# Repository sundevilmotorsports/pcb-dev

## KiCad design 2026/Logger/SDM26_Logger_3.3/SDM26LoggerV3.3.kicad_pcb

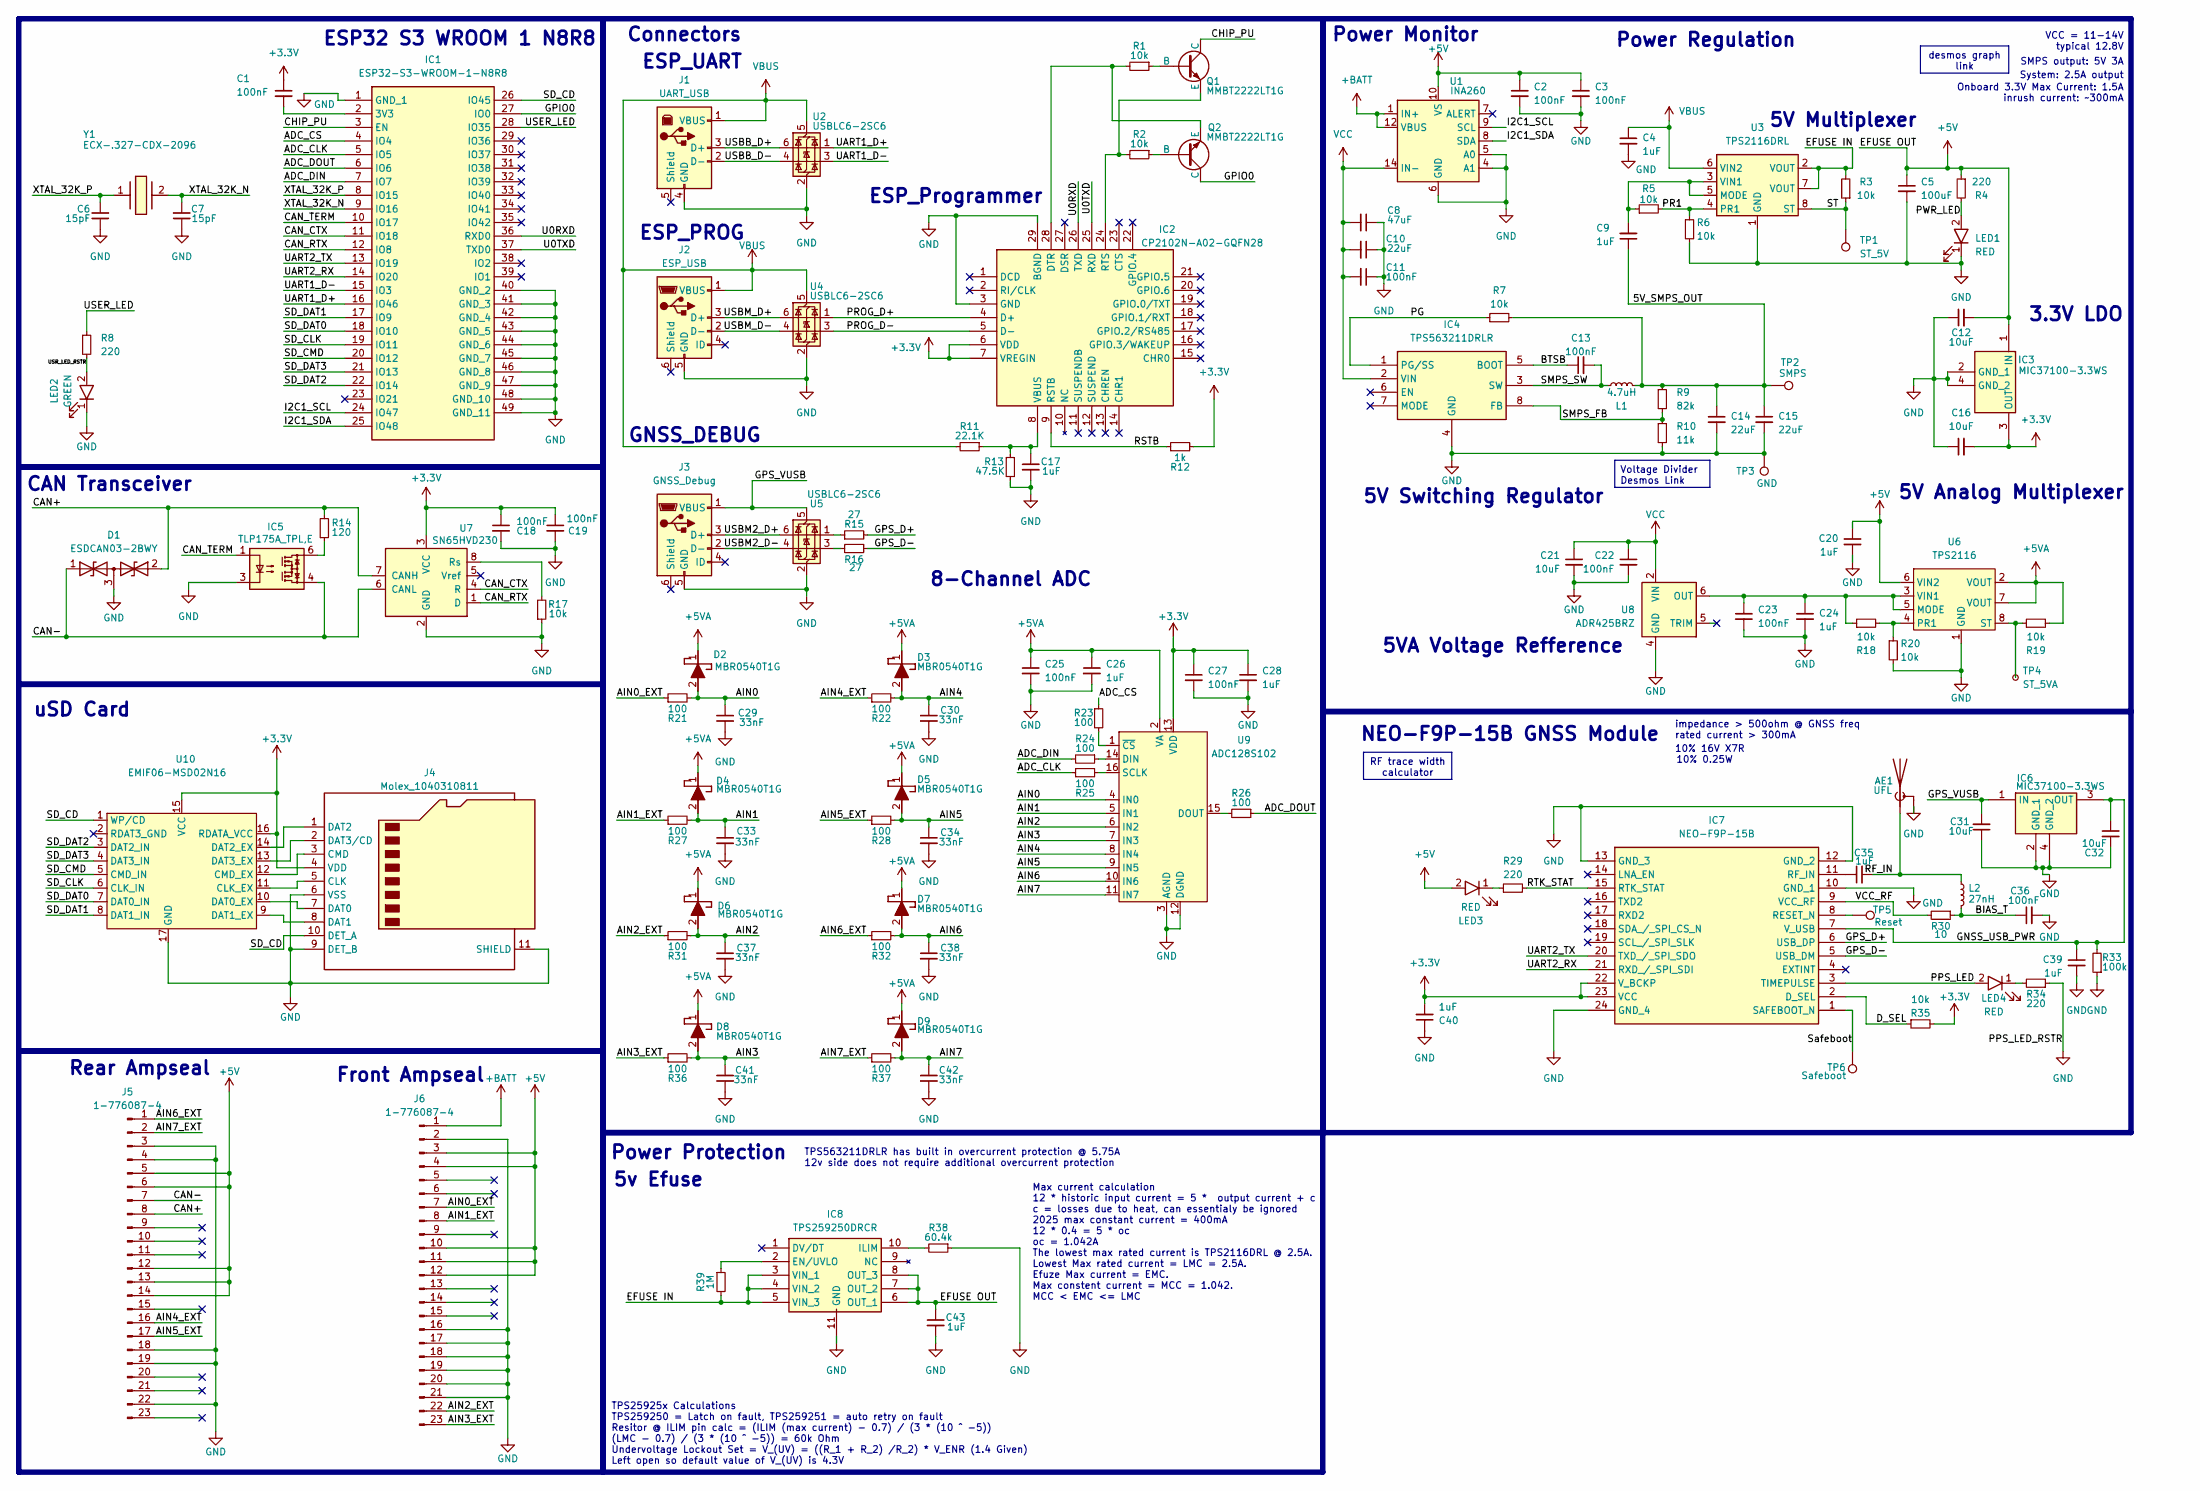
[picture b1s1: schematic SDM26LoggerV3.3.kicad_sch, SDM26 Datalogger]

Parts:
AE1: UFL; U.FL_Molex_MCRF_73412-0110_Vertical
C1, C2, C3, C11, C13, C18, C19, C22, C23, C25, C27, C36: 100nF; C_0603_1608Metric
C4, C9, C17, C20, C24, C26, C28, C35, C39, C40, C43: 1uF; C_0603_1608Metric
C5: 100uF; CP_Elec_6.3x5.9
C6, C7: 15pF; C_0603_1608Metric
C8: 47uF; CP_Elec_6.3x5.9
C10, C14, C15: 22uF; C_0603_1608Metric
C12, C16, C21, C31, C32: 10uF; C_0603_1608Metric
C29, C30, C33, C34, C37, C38, C41, C42: 33nF; C_0603_1608Metric
D1: ESDCAN03-2BWY; SOT65P210X110-3N; Mouser Part Number 511-ESDCAN03-2BWY
D2, D3, D4, D5, D6, D7, D8, D9: MBR0540T1G; SOD3716X135N; Mouser Part Number 863-MBR0540T1G
IC1: ESP32-S3-WROOM-1-N8R8; ESP32S3WROOM1N8R8; Mouser Part Number 356-EP32S3WROOM1N8R8
IC2: CP2102N-A02-GQFN28; QFN50P500X500X80-29N-D; Mouser Part Number 634-CP2102NA02GQFN28
IC3, IC6: MIC37100-3.3WS; SOT230P700X180-4N; Mouser Part Number 998-MIC37100-3.3WS
IC4: TPS563211DRLR; SOTFL50P160X60-8N; Mouser Part Number 595-TPS563211DRLR
IC5: TLP175A_TPL,E; TLP266J; Mouser Part Number 757-TLP175A(TPLE
IC7: NEO-F9P-15B; NEOF9P15B; Mouser Part Number 377-NEO-F9P-15B
IC8: TPS259250DRCR; SON50P300X300X100-11L-D; Mouser Part Number 595-TPS259250DRCR
J1: UART_USB; 67068-7041
J2: ESP_USB; USB_Micro-B_Molex-105017-0001
J3: GNSS_Debug; USB_Micro-B_Molex-105017-0001
J4: Molex_1040310811; microSD_HC_Molex_104031-0811
J5, J6: 1-776087-4; CONN23_776087_TEC
L1: 4.7uH; L_Bourns_SRP7028A_7.3x6.6mm
L2: 27nH; L_0402_1005Metric
LED1, LED3, LED4: RED; SSFLXH100LID01; Mouser Part Number 696-SSFLXH100LID01
LED2: GREEN; SSFLXH100LID01; Mouser Part Number 696-SSFLXH100LID01
Q1, Q2: MMBT2222LT1G; SOT96P237X111-3N
R1, R2, R3, R5, R6, R7, R17, R18, R19, R20, R35: 10k; R_0603_1608Metric
R4, R8, R29, R34: 220; R_0603_1608Metric
R9: 82k; R_0603_1608Metric
R10: 11k; R_0603_1608Metric
R11: 22.1K; R_0603_1608Metric
R12: 1k; R_0603_1608Metric
R13: 47.5K; R_0603_1608Metric
R14: 120; R_0603_1608Metric
R15, R16: 27; R_0603_1608Metric
R21, R22, R23, R24, R25, R26, R27, R28, R31, R32, R36, R37: 100; R_0603_1608Metric
R30: 10; R_0603_1608Metric
R33: 100k; R_0603_1608Metric
R38: 60.4k; R_0603_1608Metric
R39: 1M; R_0603_1608Metric
TP1: ST_5V; TestPoint_Pad_1.5x1.5mm
TP2: SMPS; TestPoint_Pad_1.5x1.5mm
TP3: GND; TestPoint_Pad_1.5x1.5mm
TP4: ST_5VA; TestPoint_Pad_1.5x1.5mm
TP5: Reset; TestPoint_Pad_1.5x1.5mm
TP6: Safeboot; TestPoint_Pad_1.5x1.5mm
U1: INA260; TSSOP-16_4.4x5mm_P0.65mm
U2, U4, U5: USBLC6-2SC6; SOT-23-6
U3: TPS2116DRL; SOT-583-8
U6: TPS2116; SOT-5X3
U7: SN65HVD230; SOIC-8_3.9x4.9mm_P1.27mm
U8: ADR425BRZ; SOIC-8_3.9x4.9mm_P1.27mm
U9: ADC128S102; TSSOP-16_4.4x5mm_P0.65mm
U10: EMIF06-MSD02N16; UQFN-17-3.5x1.2mm
Y1: ECX-.327-CDX-2096; ECX327CDX2096; Mouser Part Number 520-X-.327-CDX2096

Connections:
+3.3V: C1.1, C16.2, C18.1, C19.1, C27.1, C28.1, C40.2, IC2.6 (VDD), IC2.7 (VREGIN), IC3.3 (OUT), IC7.22 (V_BCKP), IC7.23 (VCC), J4.4 (VDD), R12.2, R35.2, U7.3 (VCC), U9.13 (VDD), U10.15 (VCC), U10.16 (RDATA_VCC)
+5V: C2.1, C3.1, C5.1, C12.2, C20.1, C43.1, IC3.1 (IN), IC8.6 (OUT_1), IC8.7 (OUT_2), IC8.8 (OUT_3), J5.5, J5.6, J5.12, J5.13, J5.14, J6.3, J6.4, J6.10, J6.11, J6.12, LED3.2 (A), R4.1, U1.10 (VS), U6.6 (VIN2)
+5VA: C25.1, C26.1, D2.1 (K), D3.1 (K), D4.1 (K), D5.1 (K), D6.1 (K), D7.1 (K), D8.1 (K), D9.1 (K), R19.2, U6.2 (VOUT), U6.7 (VOUT), U9.2 (VA)
+BATT: J6.1, U1.1 (IN+), U1.2 (IN+), U1.3 (IN+), U1.12 (VBUS)
/5V_SMPS_OUT: C9.1, C14.1, C15.1, L1.1, R7.2, R9.1, TP2.1
/ADC_CLK: IC1.5 (IO5), R25.1
/ADC_CS: IC1.4 (IO4), R23.1
/ADC_DIN: IC1.7 (IO7), R24.2
/ADC_DOUT: IC1.6 (IO6), R26.1
/AIN0: C29.1, D2.2 (A), R21.2, U9.4 (IN0)
/AIN0_EXT: J6.7, R21.1
/AIN1: C33.1, D4.2 (A), R27.2, U9.5 (IN1)
/AIN1_EXT: J6.8, R27.1
/AIN2: C37.1, D6.2 (A), R31.2, U9.6 (IN2)
/AIN2_EXT: J6.22, R31.1
/AIN3: C41.1, D8.2 (A), R36.2, U9.7 (IN3)
/AIN3_EXT: J6.23, R36.1
/AIN4: C30.1, D3.2 (A), R22.2, U9.8 (IN4)
/AIN4_EXT: J5.16, R22.1
/AIN5: C34.1, D5.2 (A), R28.2, U9.9 (IN5)
/AIN5_EXT: J5.17, R28.1
/AIN6: C38.1, D7.2 (A), R32.2, U9.10 (IN6)
/AIN6_EXT: J5.1, R32.1
/AIN7: C42.1, D9.2 (A), R37.2, U9.11 (IN7)
/AIN7_EXT: J5.2, R37.1
/BIAS_T: C36.1, L2.2, R30.1
/BTSB: C13.1, IC4.5 (BOOT)
/CAN+: D1.2, J5.8, R14.2, U7.7 (CANH)
/CAN-: D1.1, IC5.4, J5.7, U7.6 (CANL)
/CAN_CTX: IC1.11 (IO18), U7.4 (R)
/CAN_RTX: IC1.12 (IO8), U7.1 (D)
/CAN_TERM: IC1.10 (IO17), IC5.1
/CHIP_PU: IC1.3 (EN), Q1.1 (C)
/D_SEL: IC7.2 (D_SEL), R35.1
/EFUSE IN: IC8.3 (VIN_1), IC8.4 (VIN_2), IC8.5 (VIN_3), R3.2, R39.2, U3.2 (VOUT), U3.7 (VOUT)
/GNSS_USB_PWR: C32.1, C39.1, IC6.3 (OUT), IC7.7 (V_USB), R33.2
/GPIO0: IC1.27 (IO0), Q2.1 (C)
/GPS_D+: IC7.6 (USB_DP), R15.2
/GPS_D-: IC7.5 (USB_DM), R16.1
/GPS_VUSB: C31.2, IC6.1 (IN), J3.1 (VBUS), U5.5 (VBUS); also elsewhere on the board
/I2C1_SCL: IC1.24 (IO47), U1.9 (SCL)
/I2C1_SDA: IC1.25 (IO48), U1.8 (SDA)
/PG: IC4.1 (PG/SS), R7.1
/PPS_LED: IC7.3 (TIMEPULSE), LED4.2 (A)
/PR1: R5.2, R6.1, U3.4 (PR1)
/PROG_D+: IC2.4 (D+), U4.1 (I/O1)
/PROG_D-: IC2.5 (D-), U4.3 (I/O2)
/PWR_LED: LED1.2 (A), R4.2
/RF_IN: AE1.1 (A), C35.2, L2.1
/RSTB: IC2.9 (RSTB), R12.1
/RTK_STAT: IC7.15 (RTK_STAT), R29.2
/SD_CD: IC1.26 (IO45), J4.10 (DET_A), U10.1 (WP/CD)
/SD_CLK: IC1.19 (IO11), U10.6 (CLK_IN)
/SD_CMD: IC1.20 (IO12), U10.5 (CMD_IN)
/SD_DAT0: IC1.18 (IO10), U10.7 (DAT0_IN)
/SD_DAT1: IC1.17 (IO9), U10.8 (DAT1_IN)
/SD_DAT2: IC1.22 (IO14), U10.3 (DAT2_IN)
/SD_DAT3: IC1.21 (IO13), U10.4 (DAT3_IN)
/SMPS_FB: IC4.8 (FB), R9.2, R10.1
/SMPS_SW: C13.2, IC4.3 (SW), L1.2
/ST: R3.1, TP1.1, U3.8 (ST)
/Safeboot: IC7.1 (SAFEBOOT_N), TP6.1
/U0RXD: IC1.36 (RXD0), IC2.26 (TXD)
/U0TXD: IC1.37 (TXD0), IC2.25 (RXD)
/UART1_D+: IC1.16 (IO46), U2.1 (I/O1)
/UART1_D-: IC1.15 (IO3), U2.3 (I/O2)
/UART2_RX: IC1.14 (IO20), IC7.21 (RXD_/_SPI_SDI)
/UART2_TX: IC1.13 (IO19), IC7.20 (TXD_/_SPI_SDO)
/USBB_D+: J1.3 (D+), U2.6 (I/O1)
/USBB_D-: J1.2 (D-), U2.4 (I/O2)
/USBM2_D+: J3.3 (D+), U5.6 (I/O1)
/USBM2_D-: J3.2 (D-), U5.4 (I/O2)
/USBM_D+: J2.3 (D+), U4.6 (I/O1)
/USBM_D-: J2.2 (D-), U4.4 (I/O2)
/USER_LED: IC1.28 (IO35), R8.1
/USR_LED_RSTR: LED2.2 (A), R8.2
/VCC_RF: IC7.9 (VCC_RF), R30.2
/XTAL_32K_N: C7.2, IC1.9 (IO16), Y1.2
/XTAL_32K_P: C6.2, IC1.8 (IO15), Y1.1
GND: AE1.2 (Shield), C2.2, C3.2, C4.2, C5.2, C6.1, C7.1, C8.1, C10.1, C11.1, C12.1, C14.2, C15.2, C16.1, C17.2, C18.2, C19.2, C20.2, C21.2, C22.2, C23.2, C24.2, C25.2, C26.2, C27.2, C28.2, C29.2, C30.2, C31.1, C32.2, C33.2, C34.2, C36.2, C37.2, C38.2, C39.2, C40.1, C41.2, C42.2, C43.2, D1.3, IC1.1 (GND_1), IC1.40 (GND_2), IC1.41 (GND_3), IC1.42 (GND_4), IC1.43 (GND_5), IC1.44 (GND_6), IC1.45 (GND_7), IC1.46 (GND_8), IC1.47 (GND_9), IC1.48 (GND_10), IC1.49 (GND_11), IC2.3 (GND), IC2.29 (BGND), IC3.2 (GND_1), IC3.4 (GND_2), IC4.4 (GND), IC5.3, IC6.2 (GND_1), IC6.4 (GND_2), IC7.10 (GND_1), IC7.12 (GND_2), IC7.13 (GND_3), IC7.24 (GND_4), IC8.11 (GND), J1.4 (GND), J2.5 (GND), J3.5 (GND), J4.6 (VSS), J4.9 (DET_B), J4.11 (SHIELD), J5.3, J5.4, J5.18, J5.19, J5.22, J6.2, J6.16, J6.17, J6.18, J6.19, J6.20, J6.21, LED1.1 (K), LED2.1 (K), R6.2, R10.2, R13.2, R17.1, R20.2, R33.1, R34.1, R38.1, TP3.1, U1.4 (A1), U1.5 (A0), U1.6 (GND), U1.11 (GND), U2.2 (GND), U3.1 (GND), U4.2 (GND), U5.2 (GND), U6.1 (GND), U7.2 (GND), U8.4 (GND), U9.3 (AGND), U9.12 (DGND), U10.17 (GND); also elsewhere on the board
unnamed: C1.2, IC1.2 (3V3)
unnamed: IC2.28 (DTR), Q2.3 (E), R1.2
unnamed: IC2.24 (RTS), Q1.3 (E), R2.2
unnamed: C17.1, IC2.8 (VBUS), R11.1, R13.1
unnamed: IC5.6, R14.1
unnamed: IC7.8 (RESET_N), TP5.1
unnamed: C35.1, IC7.11 (RF_IN)
unnamed: IC8.2 (EN/UVLO), R39.1
unnamed: IC8.10 (ILIM), R38.2
unnamed: J4.5 (CLK), U10.11 (CLK_EX)
unnamed: J4.3 (CMD), U10.12 (CMD_EX)
unnamed: J4.7 (DAT0), U10.10 (DAT0_EX)
unnamed: J4.8 (DAT1), U10.9 (DAT1_EX)
unnamed: J4.1 (DAT2), U10.14 (DAT2_EX)
unnamed: J4.2 (DAT3/CD), U10.13 (DAT3_EX)
unnamed: LED3.1 (K), R29.1
unnamed: LED4.1 (K), R34.2
unnamed: Q1.2 (B), R1.1
unnamed: Q2.2 (B), R2.1
unnamed: R15.1, U5.1 (I/O1)
unnamed: R16.2, U5.3 (I/O2)
unnamed: C9.2, R5.1, U3.3 (VIN1), U3.5 (MODE)
unnamed: C23.1, C24.1, R18.1, U6.3 (VIN1), U6.5 (MODE), U8.6 (OUT)
unnamed: R18.2, R20.1, U6.4 (PR1)
unnamed: R19.1, TP4.1, U6.8 (ST)
unnamed: R17.2, U7.8 (Rs)
unnamed: R24.1, U9.14 (DIN)
unnamed: R26.2, U9.15 (DOUT)
unnamed: R25.2, U9.16 (SCLK)
unnamed: R23.2, U9.1 (~CS)
VBUS: C4.1, J1.1 (VBUS), J2.1 (VBUS), R11.2, U2.5 (VBUS), U3.6 (VIN2), U4.5 (VBUS); also elsewhere on the board
VCC: C8.2, C10.2, C11.2, C21.1, C22.1, IC4.2 (VIN), U1.14 (IN-), U1.15 (IN-), U1.16 (IN-), U8.2 (VIN)

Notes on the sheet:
Power Regulation
5V Multiplexer
CAN Transceiver
10% 16V X7R
5v Efuse
inrush current: ~300mA
5V Switching Regulator
5V Analog Multiplexer
ESP32 S3 WROOM 1 N8R8
Power Monitor
Connectors
10% 0.25W
ESP_PROG
Onboard 3.3V Max Current: 1.5A
impedance > 500ohm @ GNSS freq rated current > 300mA
Front Ampseal
3.3V LDO
VCC = 11-14V typical 12.8V
GNSS_DEBUG
Max current calculation 12 * historic input current = 5 * output current + c c = losses due to heat, can essentialy be ignored 2025 max constant current = 400mA 12 * 0.4 = 5 * oc oc = 1.042A The lowest max rated current is TPS2116DRL @ 2.5A. Lowest Max rated current = LMC = 2.5A. Efuze Max current 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
ESP_UART
TPS563211DRLR has built in overcurrent protection @ 5.75A 12v side does not require additional overcurrent protection
8-Channel ADC
uSD Card
ESP_Programmer
Power Protection
5VA Voltage Refference
SMPS output: 5V 3A
NEO-F9P-15B GNSS Module
System: 2.5A output
Rear Ampseal
TPS25925x Calculations TPS259250 = Latch on fault, TPS259251 = auto retry on fault Resitor @ ILIM pin calc = (ILIM (max current) - 0.7) / (3 * (10 ^ -5)) (LMC - 0.7) / (3 * (10 ^ -5)) = 60k Ohm Undervoltage Lockout Set = V_(UV) = ((R_1 + R_2) /R_2) * V_ENR (1.4 Given) Left open so default value of 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
desmos graph link
Voltage Divider Desmos Link
RF trace width calculator

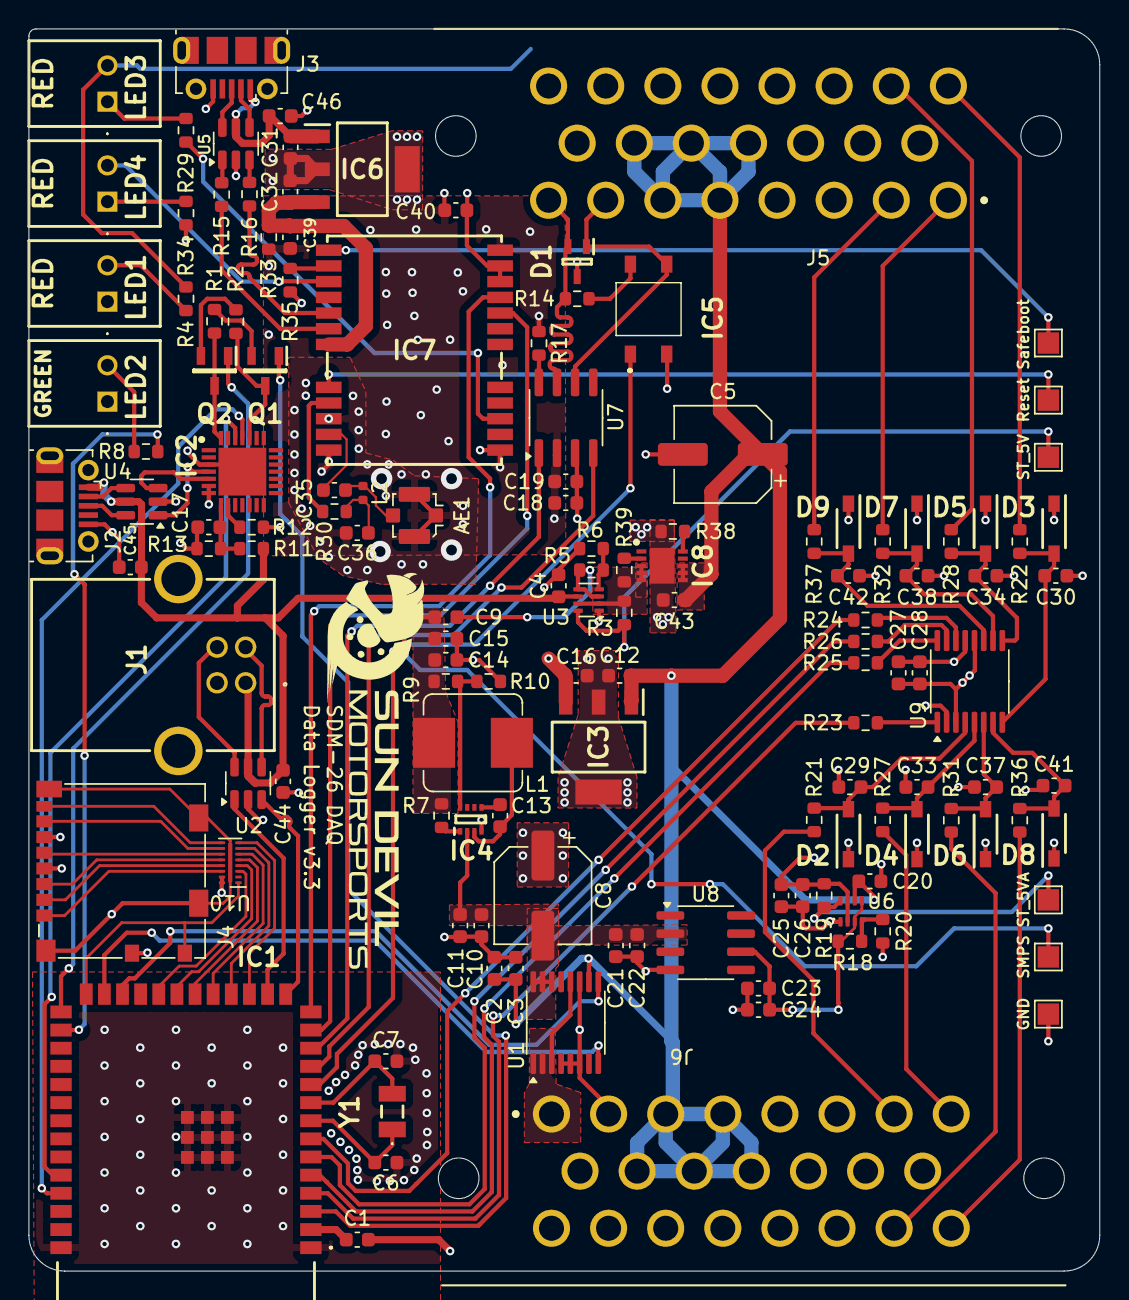
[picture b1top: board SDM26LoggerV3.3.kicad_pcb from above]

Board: 4 copper layers, 75.0 x 87.0 mm, 134 parts (0 on the bottom side), 112 nets.

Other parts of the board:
C44, C45, C46: 100nF; C_0603_1608Metric

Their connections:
/GPS_VUSB: C46.2; also elsewhere on the board
GND: C44.1, C45.1, C46.1; also elsewhere on the board
VBUS: C44.2, C45.2; also elsewhere on the board

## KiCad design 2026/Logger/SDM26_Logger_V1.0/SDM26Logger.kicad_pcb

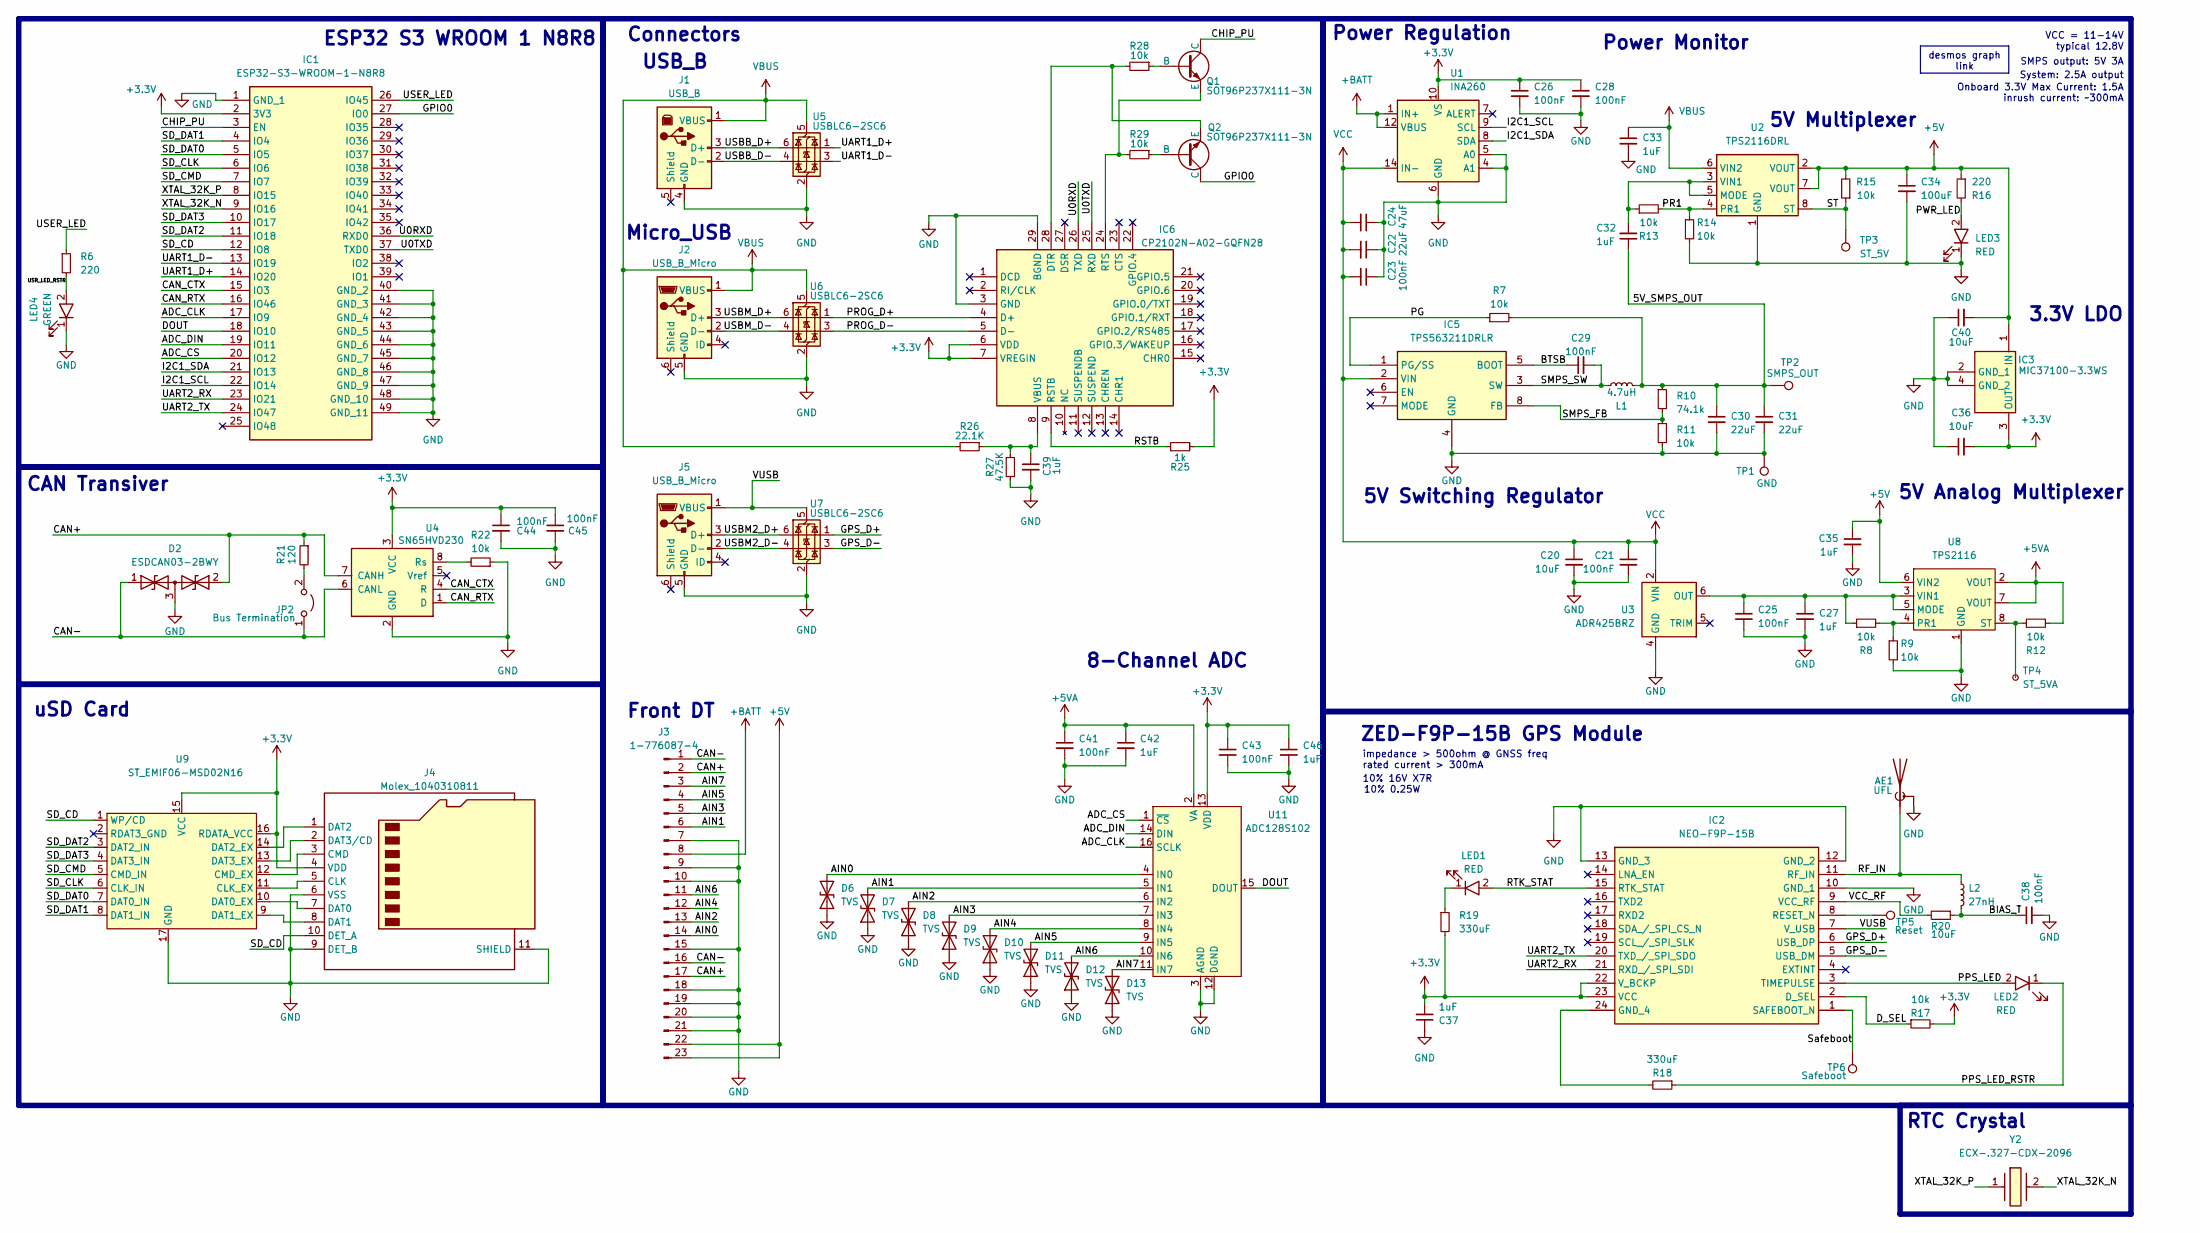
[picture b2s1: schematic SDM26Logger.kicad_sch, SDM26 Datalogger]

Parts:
AE1: UFL; U.FL_Molex_MCRF_73412-0110_Vertical
C20, C36, C40: 10uF; C_0603_1608Metric
C21, C23, C25, C26, C28, C29, C38, C41, C43, C44, C45: 100nF; C_0603_1608Metric
C22, C30, C31: 22uF; C_0603_1608Metric
C24: 47uF; CP_Elec_6.3x5.9
C27, C32, C33, C35, C37, C39, C42, C46: 1uF; C_0603_1608Metric
C34: 100uF; CP_Elec_6.3x5.9
D2: ESDCAN03-2BWY; SOT65P210X110-3N; Mouser Part Number 511-ESDCAN03-2BWY
D6, D7, D8, D9, D10, D11, D12, D13: TVS; D_SOD-323
IC1: ESP32-S3-WROOM-1-N8R8; ESP32S3WROOM1N8R8; Mouser Part Number 356-EP32S3WROOM1N8R8
IC2: NEO-F9P-15B; NEOF9P15B; Mouser Part Number 377-NEO-F9P-15B
IC3: MIC37100-3.3WS; SOT230P700X180-4N; Mouser Part Number 998-MIC37100-3.3WS
IC5: TPS563211DRLR; SOTFL50P160X60-8N; Mouser Part Number 595-TPS563211DRLR
IC6: CP2102N-A02-GQFN28; QFN50P500X500X80-29N-D; Mouser Part Number 634-CP2102NA02GQFN28
J1: USB_B; 67068-7041
J2, J5: USB_B_Micro; USB_Micro-B_Molex-105017-0001
J3: 1-776087-4; CONN23_776087_TEC
J4: Molex_1040310811; microSD_HC_Molex_104031-0811
JP2: Bus Termination; PinHeader_1x02_P2.54mm_Vertical
L1: 4.7uH; L_Bourns_SRP7028A_7.3x6.6mm
L2: 27nH; L_0402_1005Metric
LED1, LED2, LED3: RED; SSFLXH100LID01; Mouser Part Number 696-SSFLXH100LID01
LED4: GREEN; SSFLXH100LID01; Mouser Part Number 696-SSFLXH100LID01
Q1, Q2: SOT96P237X111-3N
R6, R16: 220; R_0603_1608Metric
R7, R11, R12, R13, R14, R15, R17, R22, R28, R29: 10k; R_0603_1608Metric
R8, R9: 10k; R_0402_1005Metric
R10: 74.1k; R_0603_1608Metric
R18, R19: 330uF; R_0603_1608Metric
R20: 10uF; R_0603_1608Metric
R21: 120; R_0603_1608Metric
R25: 1k; R_0603_1608Metric
R26: 22.1K; R_0603_1608Metric
R27: 47.5K; R_0603_1608Metric
TP1: GND; TestPoint_Pad_1.5x1.5mm
TP2: SMPS_OUT; TestPoint_Pad_1.5x1.5mm
TP3: ST_5V; TestPoint_Pad_1.5x1.5mm
TP4: ST_5VA; TestPoint_Pad_1.5x1.5mm
TP5: Reset; TestPoint_Pad_1.5x1.5mm
TP6: Safeboot; TestPoint_Pad_1.5x1.5mm
U1: INA260; TSSOP-16_4.4x5mm_P0.65mm
U2: TPS2116DRL; SOT-583-8
U3: ADR425BRZ; SOIC-8_3.9x4.9mm_P1.27mm
U4: SN65HVD230; SOIC-8_3.9x4.9mm_P1.27mm
U5, U6, U7: USBLC6-2SC6; SOT-23-6
U8: TPS2116; SOT-5X3
U9: ST_EMIF06-MSD02N16; UQFN-17-3.5x1.2mm
U11: ADC128S102; TSSOP-16_4.4x5mm_P0.65mm
Y2: ECX-.327-CDX-2096; ECX327CDX2096; Mouser Part Number 520-X-.327-CDX2096

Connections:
+3.3V: C26.1, C28.1, C36.2, C37.2, C43.1, C44.1, C45.1, C46.1, IC1.2 (3V3), IC2.22 (V_BCKP), IC2.23 (VCC), IC3.3 (OUT), IC6.6 (VDD), IC6.7 (VREGIN), J4.4 (VDD), R17.2, R19.2, R25.2, U1.10 (VS), U4.3 (VCC), U9.15 (VCC), U9.16 (RDATA_VCC), U11.13 (VDD)
+5V: C34.1, C35.1, C40.2, IC3.1 (IN), J3.22, J3.23, R15.2, R16.1, U2.2 (VOUT), U2.7 (VOUT), U8.6 (VIN2)
+5VA: C41.1, C42.1, R12.2, U8.2 (VOUT), U8.7 (VOUT), U11.2 (VA)
+BATT: J3.8, U1.1 (IN+), U1.2 (IN+), U1.3 (IN+), U1.12 (VBUS)
/5V_SMPS_OUT: C30.1, C31.1, C32.1, L1.1, R7.2, R10.1, TP2.1
/ADC_CLK: IC1.17 (IO9), U11.16 (SCLK)
/ADC_CS: IC1.20 (IO12), U11.1 (~CS)
/ADC_DIN: IC1.19 (IO11), U11.14 (DIN)
/AIN0: D6.2 (A2), J3.14, U11.4 (IN0)
/AIN1: D7.2 (A2), J3.6, U11.5 (IN1)
/AIN2: D8.2 (A2), J3.13, U11.6 (IN2)
/AIN3: D9.2 (A2), J3.5, U11.7 (IN3)
/AIN4: D10.2 (A2), J3.12, U11.8 (IN4)
/AIN5: D11.2 (A2), J3.4, U11.9 (IN5)
/AIN6: D12.2 (A2), J3.11, U11.10 (IN6)
/AIN7: D13.2 (A2), J3.3, U11.11 (IN7)
/BIAS_T: C38.1, L2.2, R20.1
/BTSB: C29.1, IC5.5 (BOOT)
/CAN+: D2.2, J3.2, J3.17, R21.1, U4.7 (CANH)
/CAN-: D2.1, J3.1, J3.16, JP2.1 (A), U4.6 (CANL)
/CAN_CTX: IC1.15 (IO3), U4.4 (R)
/CAN_RTX: IC1.16 (IO46), U4.1 (D)
/CHIP_PU: IC1.3 (EN), Q1.1 (C)
/DOUT: IC1.18 (IO10), U11.15 (DOUT)
/D_SEL: IC2.2 (D_SEL), R17.1
/GPIO0: IC1.27 (IO0), Q2.1 (C)
/GPS_D+: IC2.6 (USB_DP), U7.1 (I/O1)
/GPS_D-: IC2.5 (USB_DM), U7.3 (I/O2)
/I2C1_SCL: IC1.22 (IO14), U1.9 (SCL)
/I2C1_SDA: IC1.21 (IO13), U1.8 (SDA)
/PG: IC5.1 (PG/SS), R7.1
/PPS_LED: IC2.3 (TIMEPULSE), LED2.2 (A)
/PPS_LED_RSTR: LED2.1 (K), R18.1
/PR1: R13.2, R14.1, U2.4 (PR1)
/PROG_D+: IC6.4 (D+), U6.1 (I/O1)
/PROG_D-: IC6.5 (D-), U6.3 (I/O2)
/PWR_LED: LED3.2 (A), R16.2
/RF_IN: AE1.1 (A), IC2.11 (RF_IN), L2.1
/RSTB: IC6.9 (RSTB), R25.1
/RTK_STAT: IC2.15 (RTK_STAT), LED1.2 (A)
/SD_CD: IC1.12 (IO8), J4.10 (DET_A), U9.1 (WP/CD)
/SD_CLK: IC1.6 (IO6), U9.6 (CLK_IN)
/SD_CMD: IC1.7 (IO7), U9.5 (CMD_IN)
/SD_DAT0: IC1.5 (IO5), U9.7 (DAT0_IN)
/SD_DAT1: IC1.4 (IO4), U9.8 (DAT1_IN)
/SD_DAT2: IC1.11 (IO18), U9.3 (DAT2_IN)
/SD_DAT3: IC1.10 (IO17), U9.4 (DAT3_IN)
/SMPS_FB: IC5.8 (FB), R10.2, R11.1
/SMPS_SW: C29.2, IC5.3 (SW), L1.2
/ST: R15.1, TP3.1, U2.8 (ST)
/Safeboot: IC2.1 (SAFEBOOT_N), TP6.1
/U0RXD: IC1.36 (RXD0), IC6.26 (TXD)
/U0TXD: IC1.37 (TXD0), IC6.25 (RXD)
/UART1_D+: IC1.14 (IO20), U5.1 (I/O1)
/UART1_D-: IC1.13 (IO19), U5.3 (I/O2)
/UART2_RX: IC1.23 (IO21), IC2.21 (RXD_/_SPI_SDI)
/UART2_TX: IC1.24 (IO47), IC2.20 (TXD_/_SPI_SDO)
/USBB_D+: J1.3 (D+), U5.6 (I/O1)
/USBB_D-: J1.2 (D-), U5.4 (I/O2)
/USBM2_D+: J5.3 (D+), U7.6 (I/O1)
/USBM2_D-: J5.2 (D-), U7.4 (I/O2)
/USBM_D+: J2.3 (D+), U6.6 (I/O1)
/USBM_D-: J2.2 (D-), U6.4 (I/O2)
/USER_LED: IC1.26 (IO45), R6.1
/USR_LED_RSTR: LED4.2 (A), R6.2
/VCC_RF: IC2.9 (VCC_RF), R20.2
/VUSB: IC2.7 (V_USB), J5.1 (VBUS), U7.5 (VBUS)
/XTAL_32K_N: IC1.9 (IO16), Y2.2
/XTAL_32K_P: IC1.8 (IO15), Y2.1
GND: AE1.2 (Shield), C20.2, C21.2, C22.1, C23.1, C24.1, C25.2, C26.2, C27.2, C28.2, C30.2, C31.2, C33.2, C34.2, C35.2, C36.1, C37.1, C38.2, C39.2, C40.1, C41.2, C42.2, C43.2, C44.2, C45.2, C46.2, D2.3, D6.1 (A1), D7.1 (A1), D8.1 (A1), D9.1 (A1), D10.1 (A1), D11.1 (A1), D12.1 (A1), D13.1 (A1), IC1.1 (GND_1), IC1.40 (GND_2), IC1.41 (GND_3), IC1.42 (GND_4), IC1.43 (GND_5), IC1.44 (GND_6), IC1.45 (GND_7), IC1.46 (GND_8), IC1.47 (GND_9), IC1.48 (GND_10), IC1.49 (GND_11), IC2.10 (GND_1), IC2.12 (GND_2), IC2.13 (GND_3), IC3.2 (GND_1), IC3.4 (GND_2), IC5.4 (GND), IC6.3 (GND), IC6.29 (BGND), J1.4 (GND), J2.5 (GND), J3.7, J3.9, J3.10, J3.15, J3.18, J3.19, J3.20, J3.21, J4.6 (VSS), J4.9 (DET_B), J4.11 (SHIELD), J5.5 (GND), LED3.1 (K), LED4.1 (K), R9.2, R11.2, R14.2, R22.1, R27.2, TP1.1, U1.4 (A1), U1.5 (A0), U1.6 (GND), U1.11 (GND), U2.1 (GND), U3.4 (GND), U4.2 (GND), U5.2 (GND), U6.2 (GND), U7.2 (GND), U8.1 (GND), U9.17 (GND), U11.3 (AGND), U11.12 (DGND)
unnamed: IC2.24 (GND_4), R18.2
unnamed: IC2.8 (RESET_N), TP5.1
unnamed: IC6.28 (DTR), Q2.3 (E), R28.2
unnamed: IC6.24 (RTS), Q1.3 (E), R29.2
unnamed: C39.1, IC6.8 (VBUS), R26.1, R27.1
unnamed: J4.5 (CLK), U9.11 (CLK_EX)
unnamed: J4.3 (CMD), U9.12 (CMD_EX)
unnamed: J4.7 (DAT0), U9.10 (DAT0_EX)
unnamed: J4.8 (DAT1), U9.9 (DAT1_EX)
unnamed: J4.1 (DAT2), U9.14 (DAT2_EX)
unnamed: J4.2 (DAT3/CD), U9.13 (DAT3_EX)
unnamed: JP2.2 (B), R21.2
unnamed: LED1.1 (K), R19.1
unnamed: Q1.2 (B), R28.1
unnamed: Q2.2 (B), R29.1
unnamed: C32.2, R13.1, U2.3 (VIN1), U2.5 (MODE)
unnamed: C25.1, C27.1, R8.1, U3.6 (OUT), U8.3 (VIN1), U8.5 (MODE)
unnamed: R22.2, U4.8 (Rs)
unnamed: R8.2, R9.1, U8.4 (PR1)
unnamed: R12.1, TP4.1, U8.8 (ST)
VBUS: C33.1, J1.1 (VBUS), J2.1 (VBUS), R26.2, U2.6 (VIN2), U5.5 (VBUS), U6.5 (VBUS)
VCC: C20.1, C21.1, C22.2, C23.2, C24.2, IC5.2 (VIN), U1.14 (IN-), U1.15 (IN-), U1.16 (IN-), U3.2 (VIN)

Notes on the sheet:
Power Regulation
5V Multiplexer
CAN Transiver
10% 16V X7R
inrush current: ~300mA
5V Switching Regulator
5V Analog Multiplexer
ESP32 S3 WROOM 1 N8R8
Power Monitor
RTC Crystal
Connectors
10% 0.25W
Micro_USB
Onboard 3.3V Max Current: 1.5A
impedance > 500ohm @ GNSS freq rated current > 300mA
Front DT
3.3V LDO
VCC = 11-14V typical 12.8V
USB_B
8-Channel ADC
uSD Card
SMPS output: 5V 3A
ZED-F9P-15B GPS Module
System: 2.5A output
desmos graph link

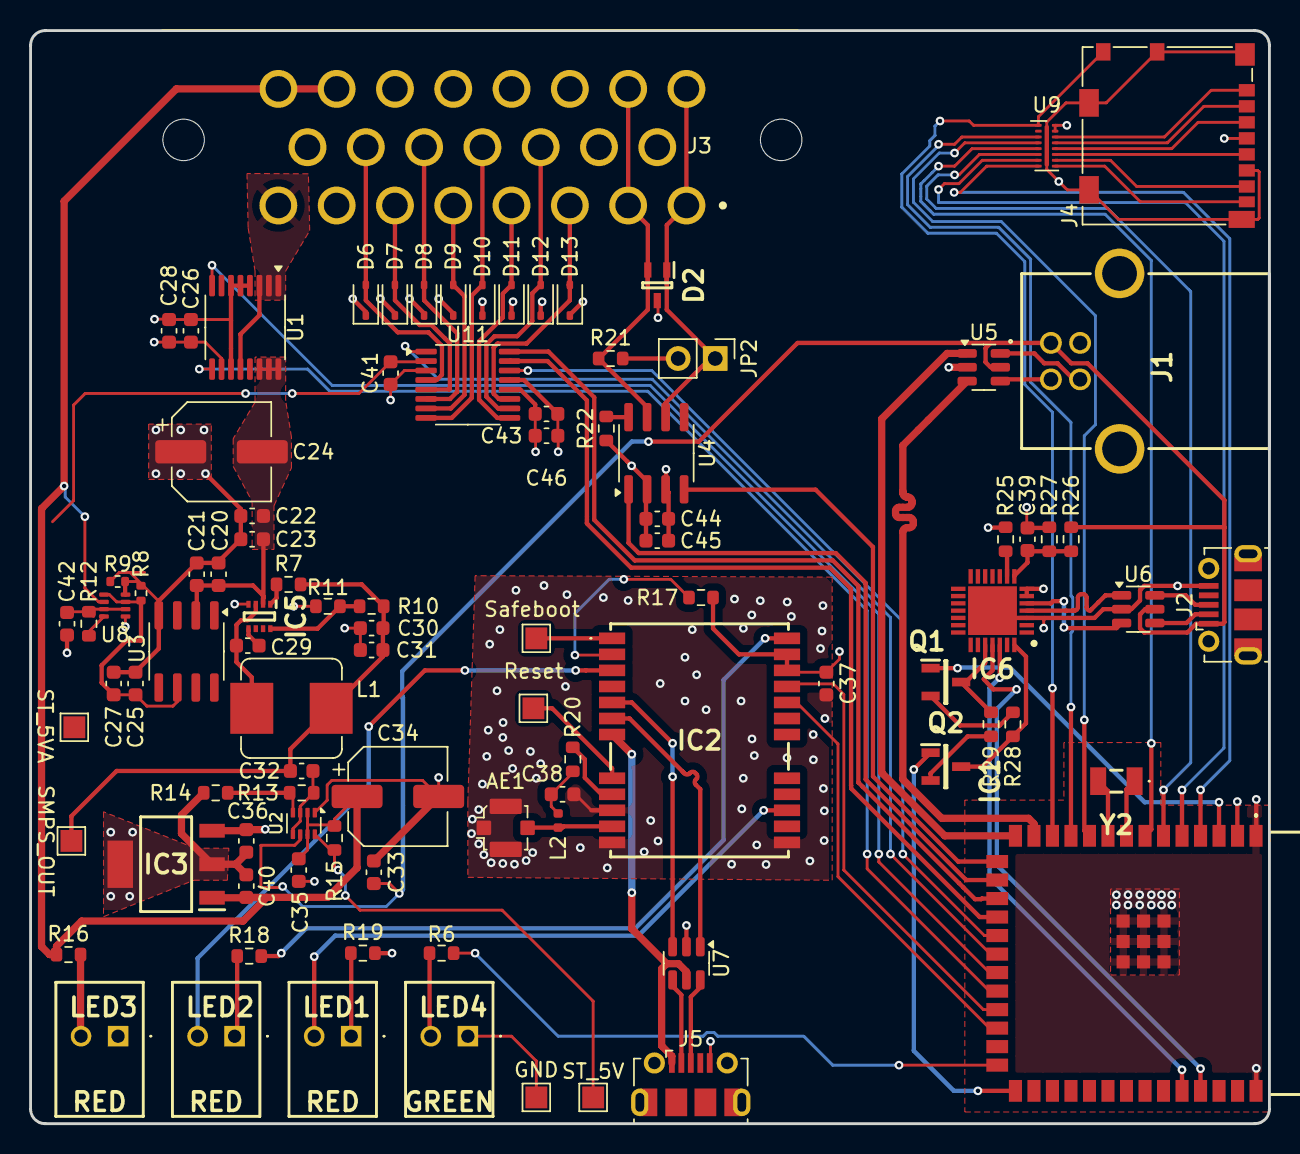
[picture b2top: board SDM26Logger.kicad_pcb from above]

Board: 4 copper layers, 85.0 x 75.0 mm, 95 parts (0 on the bottom side), 92 nets.
